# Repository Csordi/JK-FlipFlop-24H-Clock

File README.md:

# JK-FlipFlop-24H-Clock
24H TTL Clock only with TTL integrated circuits.

- 24H clock (no AM/PM mode)
- Time format: HH:MM:SS
- Red 7segment displays
- 6-18V DC IN
- Almost fully through-hole design (only one component is SMD)

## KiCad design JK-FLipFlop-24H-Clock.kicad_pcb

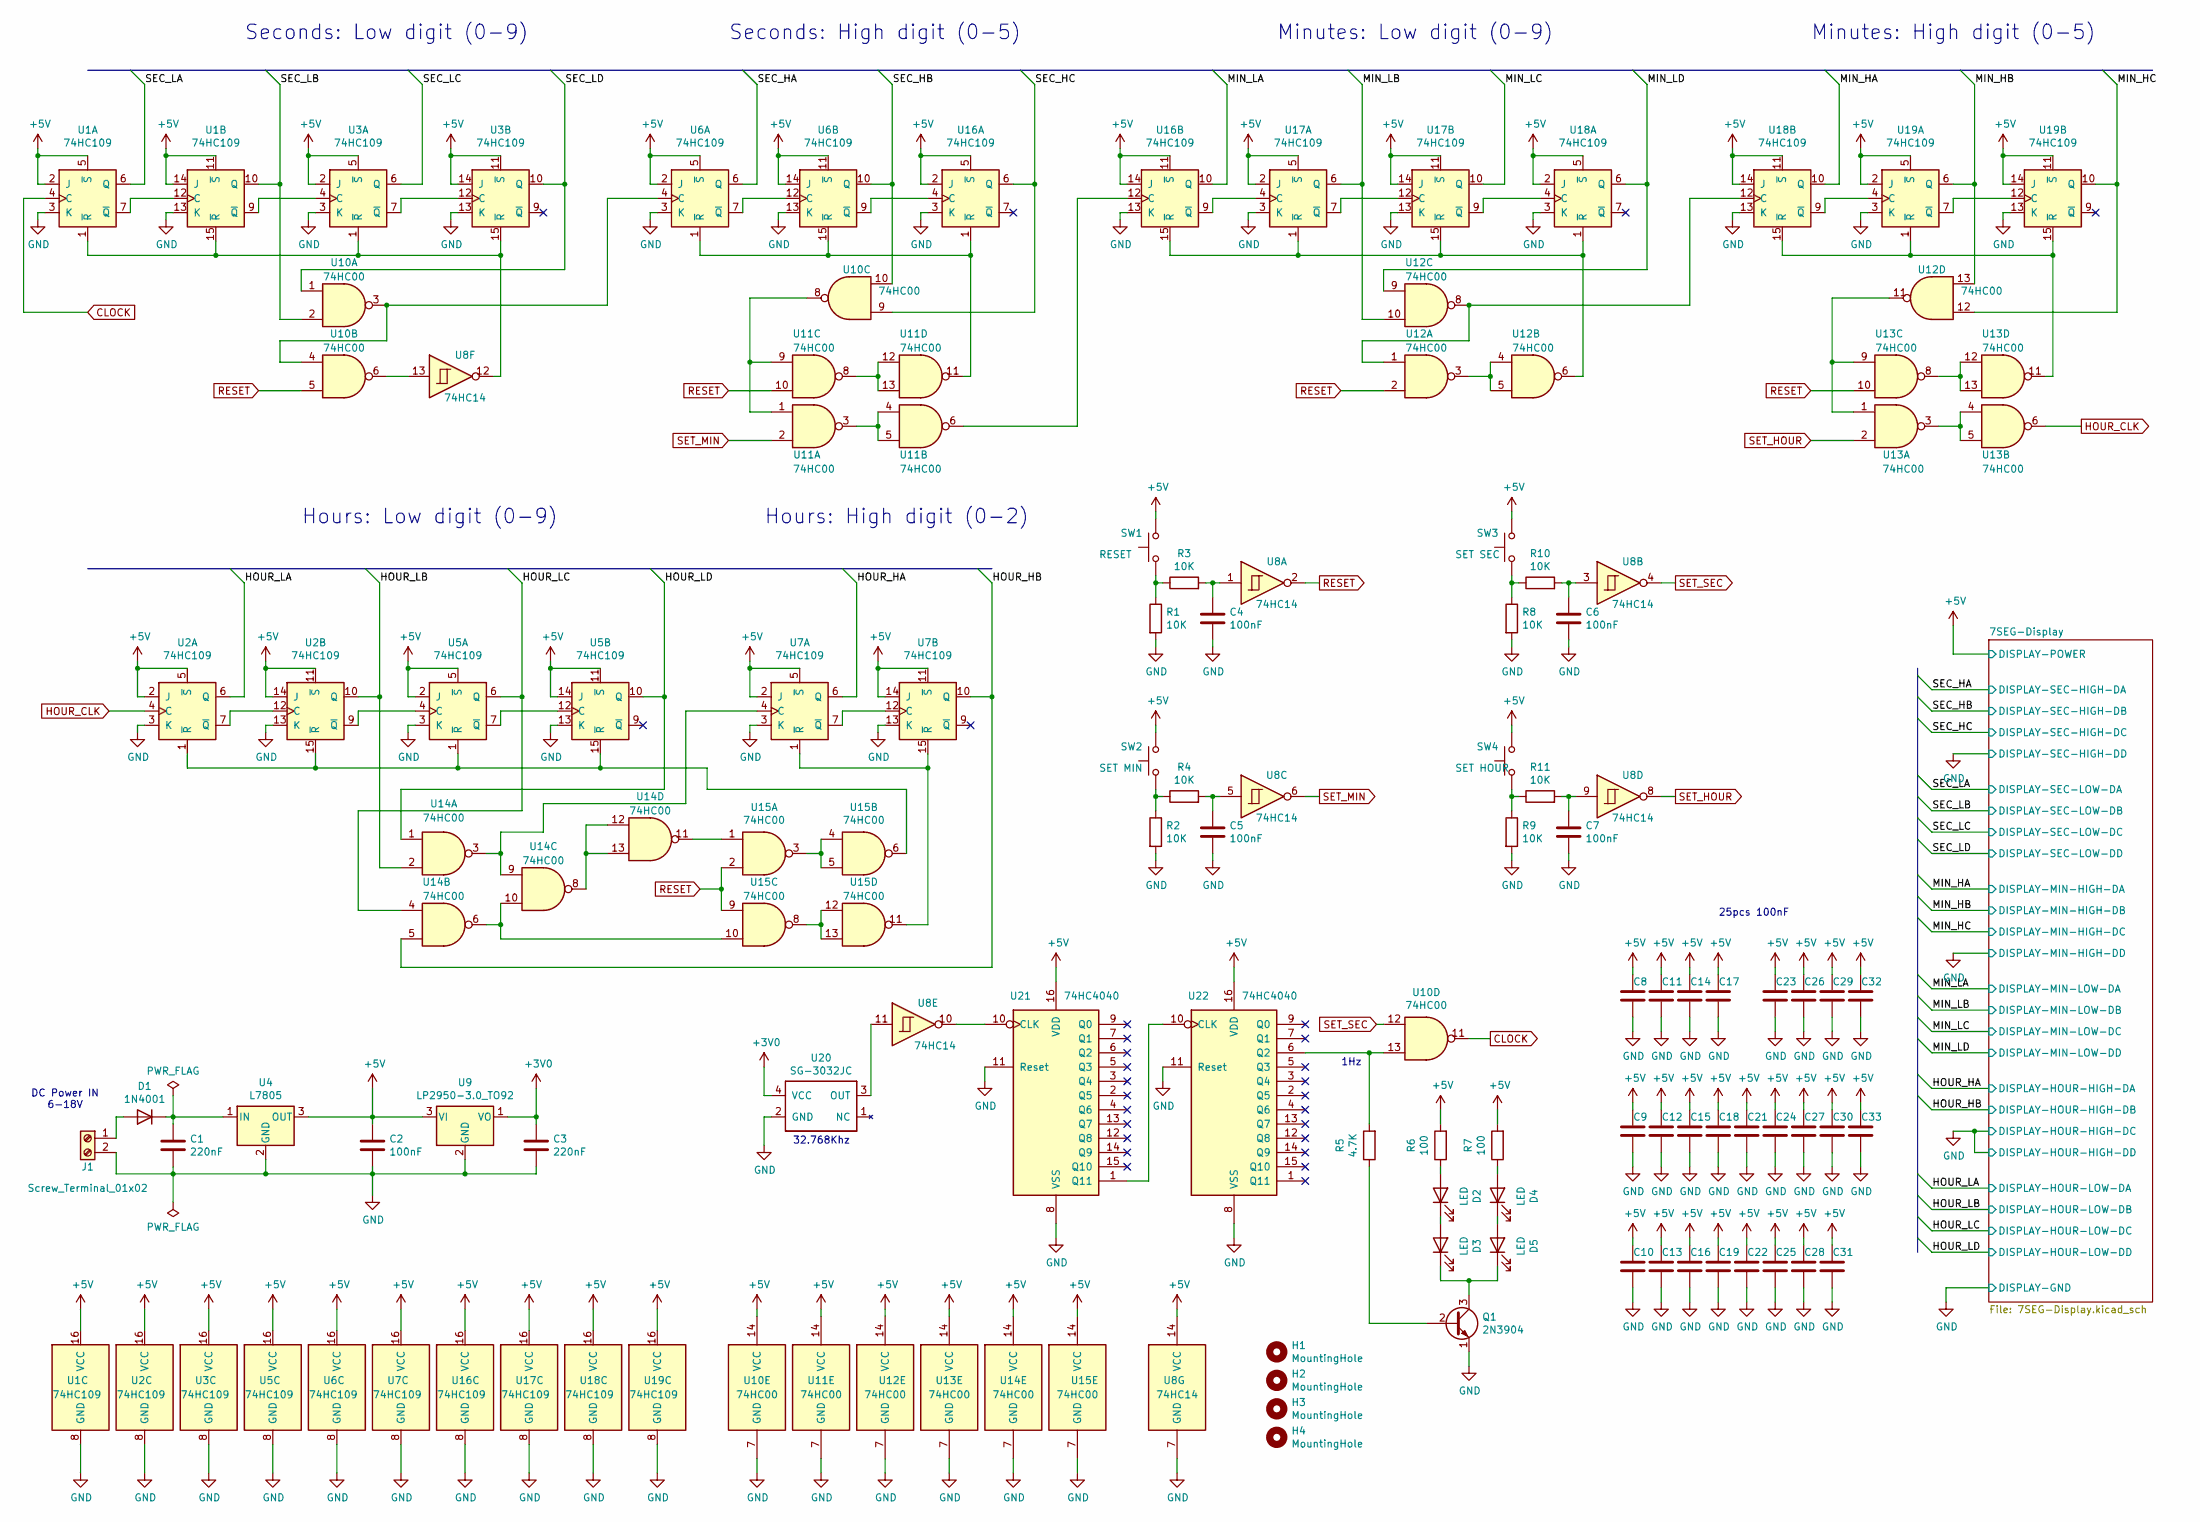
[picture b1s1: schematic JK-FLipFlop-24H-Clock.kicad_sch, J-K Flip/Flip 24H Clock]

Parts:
C1, C3: 220nF; C_Disc_D5.1mm_W3.2mm_P5.00mm
C2, C4, C5, C6, C7, C8, C9, C10, C11, C12, C13, C14, C15, C16, C17, C18, C19, C21, C22, C23, C24, C25, C26, C27, C28, C29, C30, C31, C32, C33: 100nF; C_Disc_D5.1mm_W3.2mm_P5.00mm
D1: 1N4001; D_DO-41_SOD81_P10.16mm_Horizontal
D2, D3, D4, D5: LED; LED_D3.0mm
H1, H2, H3, H4: MountingHole; MountingHole_2.2mm_M2
J1: Screw_Terminal_01x02; TerminalBlock_Altech_AK300-2_P5.00mm
Q1: 2N3904; TO-92_Inline_Wide
R1, R2, R3, R4, R8, R9, R10, R11: 10K; R_Axial_DIN0204_L3.6mm_D1.6mm_P5.08mm_Horizontal
R5: 4.7K; R_Axial_DIN0204_L3.6mm_D1.6mm_P5.08mm_Horizontal
R6, R7: 100; R_Axial_DIN0204_L3.6mm_D1.6mm_P5.08mm_Horizontal
SW1: RESET; SW_PUSH_6mm
SW2: SET MIN; SW_PUSH_6mm
SW3: SET SEC; SW_PUSH_6mm
SW4: SET HOUR; SW_PUSH_6mm
U1, U2, U3, U5, U6, U7, U16, U17, U18, U19: 74HC109; DIP-16_W7.62mm
U4: L7805; TO-220-3_Vertical
U8: 74HC14; DIP-14_W7.62mm
U9: LP2950-3.0_TO92; TO-92_Inline_Wide
U10, U11, U12, U13, U14, U15: 74HC00; DIP-14_W7.62mm
U20: SG-3032JC; SG-3030JC
U21, U22: 74HC4040; DIP-16_W7.62mm

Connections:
+3V0: C3.1, U9.1 (VO), U20.4 (VCC)
+5V: C2.1, C8.1, C9.1, C10.1, C11.1, C12.1, C13.1, C14.1, C15.1, C16.1, C17.1, C18.1, C19.1, C21.1, C22.1, C23.1, C24.1, C25.1, C26.1, C27.1, C28.1, C29.1, C30.1, C31.1, C32.1, C33.1, R6.2, R7.2, SW1.2, SW2.2, SW3.2, SW4.2, U1.2 (J), U1.5 (~S), U1.11 (~S), U1.14 (J), U1.16 (VCC), U2.2 (J), U2.5 (~S), U2.11 (~S), U2.14 (J), U2.16 (VCC), U3.2 (J), U3.5 (~S), U3.11 (~S), U3.14 (J), U3.16 (VCC), U4.3 (OUT), U5.2 (J), U5.5 (~S), U5.11 (~S), U5.14 (J), U5.16 (VCC), U6.2 (J), U6.5 (~S), U6.11 (~S), U6.14 (J), U6.16 (VCC), U7.2 (J), U7.5 (~S), U7.11 (~S), U7.14 (J), U7.16 (VCC), U8.14 (VCC), U9.3 (VI), U10.14 (VCC), U11.14 (VCC), U12.14 (VCC), U13.14 (VCC), U14.14 (VCC), U15.14 (VCC), U16.2 (J), U16.5 (~S), U16.11 (~S), U16.14 (J), U16.16 (VCC), U17.2 (J), U17.5 (~S), U17.11 (~S), U17.14 (J), U17.16 (VCC), U18.2 (J), U18.5 (~S), U18.11 (~S), U18.14 (J), U18.16 (VCC), U19.2 (J), U19.5 (~S), U19.11 (~S), U19.14 (J), U19.16 (VCC), U21.16 (VDD), U22.16 (VDD); also elsewhere on the board
/HOUR_HA: U7.6 (Q); also elsewhere on the board
/HOUR_HB: U7.10 (Q), U14.5; also elsewhere on the board
/HOUR_LA: U2.6 (Q); also elsewhere on the board
/HOUR_LB: U2.10 (Q), U14.2; also elsewhere on the board
/HOUR_LC: U5.6 (Q), U14.4; also elsewhere on the board
/HOUR_LD: U5.10 (Q), U14.1; also elsewhere on the board
/MIN_HA: U18.10 (Q); also elsewhere on the board
/MIN_HB: U12.13, U19.6 (Q); also elsewhere on the board
/MIN_HC: U12.12, U19.10 (Q); also elsewhere on the board
/MIN_LA: U16.10 (Q); also elsewhere on the board
/MIN_LB: U12.10, U17.6 (Q); also elsewhere on the board
/MIN_LC: U17.10 (Q); also elsewhere on the board
/MIN_LD: U12.9, U18.6 (Q); also elsewhere on the board
/SEC_HA: U6.6 (Q); also elsewhere on the board
/SEC_HB: U6.10 (Q), U10.10; also elsewhere on the board
/SEC_HC: U10.9, U16.6 (Q); also elsewhere on the board
/SEC_LA: U1.6 (Q); also elsewhere on the board
/SEC_LB: U1.10 (Q), U10.2; also elsewhere on the board
/SEC_LC: U3.6 (Q); also elsewhere on the board
/SEC_LD: U3.10 (Q), U10.1; also elsewhere on the board
CLOCK: U1.4 (C), U10.11
GND: C1.2, C2.2, C3.2, C4.2, C5.2, C6.2, C7.2, C8.2, C9.2, C10.2, C11.2, C12.2, C13.2, C14.2, C15.2, C16.2, C17.2, C18.2, C19.2, C21.2, C22.2, C23.2, C24.2, C25.2, C26.2, C27.2, C28.2, C29.2, C30.2, C31.2, C32.2, C33.2, J1.2, Q1.1 (E), R1.2, R2.2, R8.2, R9.2, U1.3 (K), U1.8 (GND), U1.13 (K), U2.3 (K), U2.8 (GND), U2.13 (K), U3.3 (K), U3.8 (GND), U3.13 (K), U4.2 (GND), U5.3 (K), U5.8 (GND), U5.13 (K), U6.3 (K), U6.8 (GND), U6.13 (K), U7.3 (K), U7.8 (GND), U7.13 (K), U8.7 (GND), U9.2 (GND), U10.7 (GND), U11.7 (GND), U12.7 (GND), U13.7 (GND), U14.7 (GND), U15.7 (GND), U16.3 (K), U16.8 (GND), U16.13 (K), U17.3 (K), U17.8 (GND), U17.13 (K), U18.3 (K), U18.8 (GND), U18.13 (K), U19.3 (K), U19.8 (GND), U19.13 (K), U20.2 (GND), U21.8 (VSS), U21.11 (Reset), U22.8 (VSS), U22.11 (Reset); also elsewhere on the board
HOUR_CLK: U2.4 (C), U13.6
unnamed: C1.1, D1.1 (K), U4.1 (IN)
unnamed: C4.1, R3.2, U8.1
unnamed: C5.1, R4.2, U8.5
unnamed: C6.1, R10.2, U8.3
unnamed: C7.1, R11.2, U8.9
unnamed: D1.2 (A), J1.1
unnamed: D2.1 (K), D3.2 (A)
unnamed: D2.2 (A), R6.1
unnamed: D3.1 (K), D5.1 (K), Q1.3 (C)
unnamed: D4.1 (K), D5.2 (A)
unnamed: D4.2 (A), R7.1
unnamed: Q1.2 (B), R5.1
unnamed: R1.1, R3.1, SW1.1
unnamed: R2.1, R4.1, SW2.1
unnamed: R5.2, U10.13, U22.6 (Q2)
unnamed: R8.1, R10.1, SW3.1
unnamed: R9.1, R11.1, SW4.1
unnamed: U1.1 (~R), U1.15 (~R), U3.1 (~R), U3.15 (~R), U8.12
unnamed: U1.9 (~Q), U3.4 (C)
unnamed: U1.7 (~Q), U1.12 (C)
unnamed: U2.9 (~Q), U5.4 (C)
unnamed: U2.7 (~Q), U2.12 (C)
unnamed: U3.7 (~Q), U3.12 (C)
unnamed: U5.7 (~Q), U5.12 (C)
unnamed: U6.7 (~Q), U6.12 (C)
unnamed: U7.7 (~Q), U7.12 (C)
unnamed: U6.4 (C), U10.3, U10.4
unnamed: U8.13, U10.6
unnamed: U10.8, U11.1, U11.9
unnamed: U11.3, U11.4, U11.5
unnamed: U11.6, U16.12 (C)
unnamed: U6.1 (~R), U6.15 (~R), U11.11, U16.1 (~R)
unnamed: U11.8, U11.12, U11.13
unnamed: U12.1, U12.8, U18.12 (C)
unnamed: U12.3, U12.4, U12.5
unnamed: U12.6, U16.15 (~R), U17.1 (~R), U17.15 (~R), U18.1 (~R)
unnamed: U12.11, U13.1, U13.9
unnamed: U13.3, U13.4, U13.5
unnamed: U13.11, U18.15 (~R), U19.1 (~R), U19.15 (~R)
unnamed: U13.8, U13.12, U13.13
unnamed: U7.4 (C), U14.3, U14.9
unnamed: U14.6, U14.10, U15.10
unnamed: U14.11, U15.1
unnamed: U14.8, U14.12, U14.13
unnamed: U15.3, U15.4, U15.5
unnamed: U2.1 (~R), U2.15 (~R), U5.1 (~R), U5.15 (~R), U15.6
unnamed: U7.1 (~R), U7.15 (~R), U15.11
unnamed: U15.8, U15.12, U15.13
unnamed: U6.9 (~Q), U16.4 (C)
unnamed: U16.9 (~Q), U17.4 (C)
unnamed: U17.9 (~Q), U18.4 (C)
unnamed: U17.7 (~Q), U17.12 (C)
unnamed: U18.9 (~Q), U19.4 (C)
unnamed: U19.7 (~Q), U19.12 (C)
unnamed: U8.11, U20.3 (OUT)
unnamed: U21.1 (Q11), U22.10 (CLK)
unnamed: U8.10, U21.10 (CLK)
RESET: U8.2, U10.5, U11.10, U12.2, U13.10, U15.2, U15.9
SET_HOUR: U8.8, U13.2
SET_MIN: U8.6, U11.2
SET_SEC: U8.4, U10.12

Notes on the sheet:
Hours: High digit (0-2)
Minutes: High digit (0-5)
Seconds: High digit (0-5)
1Hz
DC Power IN 6-18V
25pcs 100nF
Hours: Low digit (0-9)
32.768Khz
Seconds: Low digit (0-9)
Minutes: Low digit (0-9)

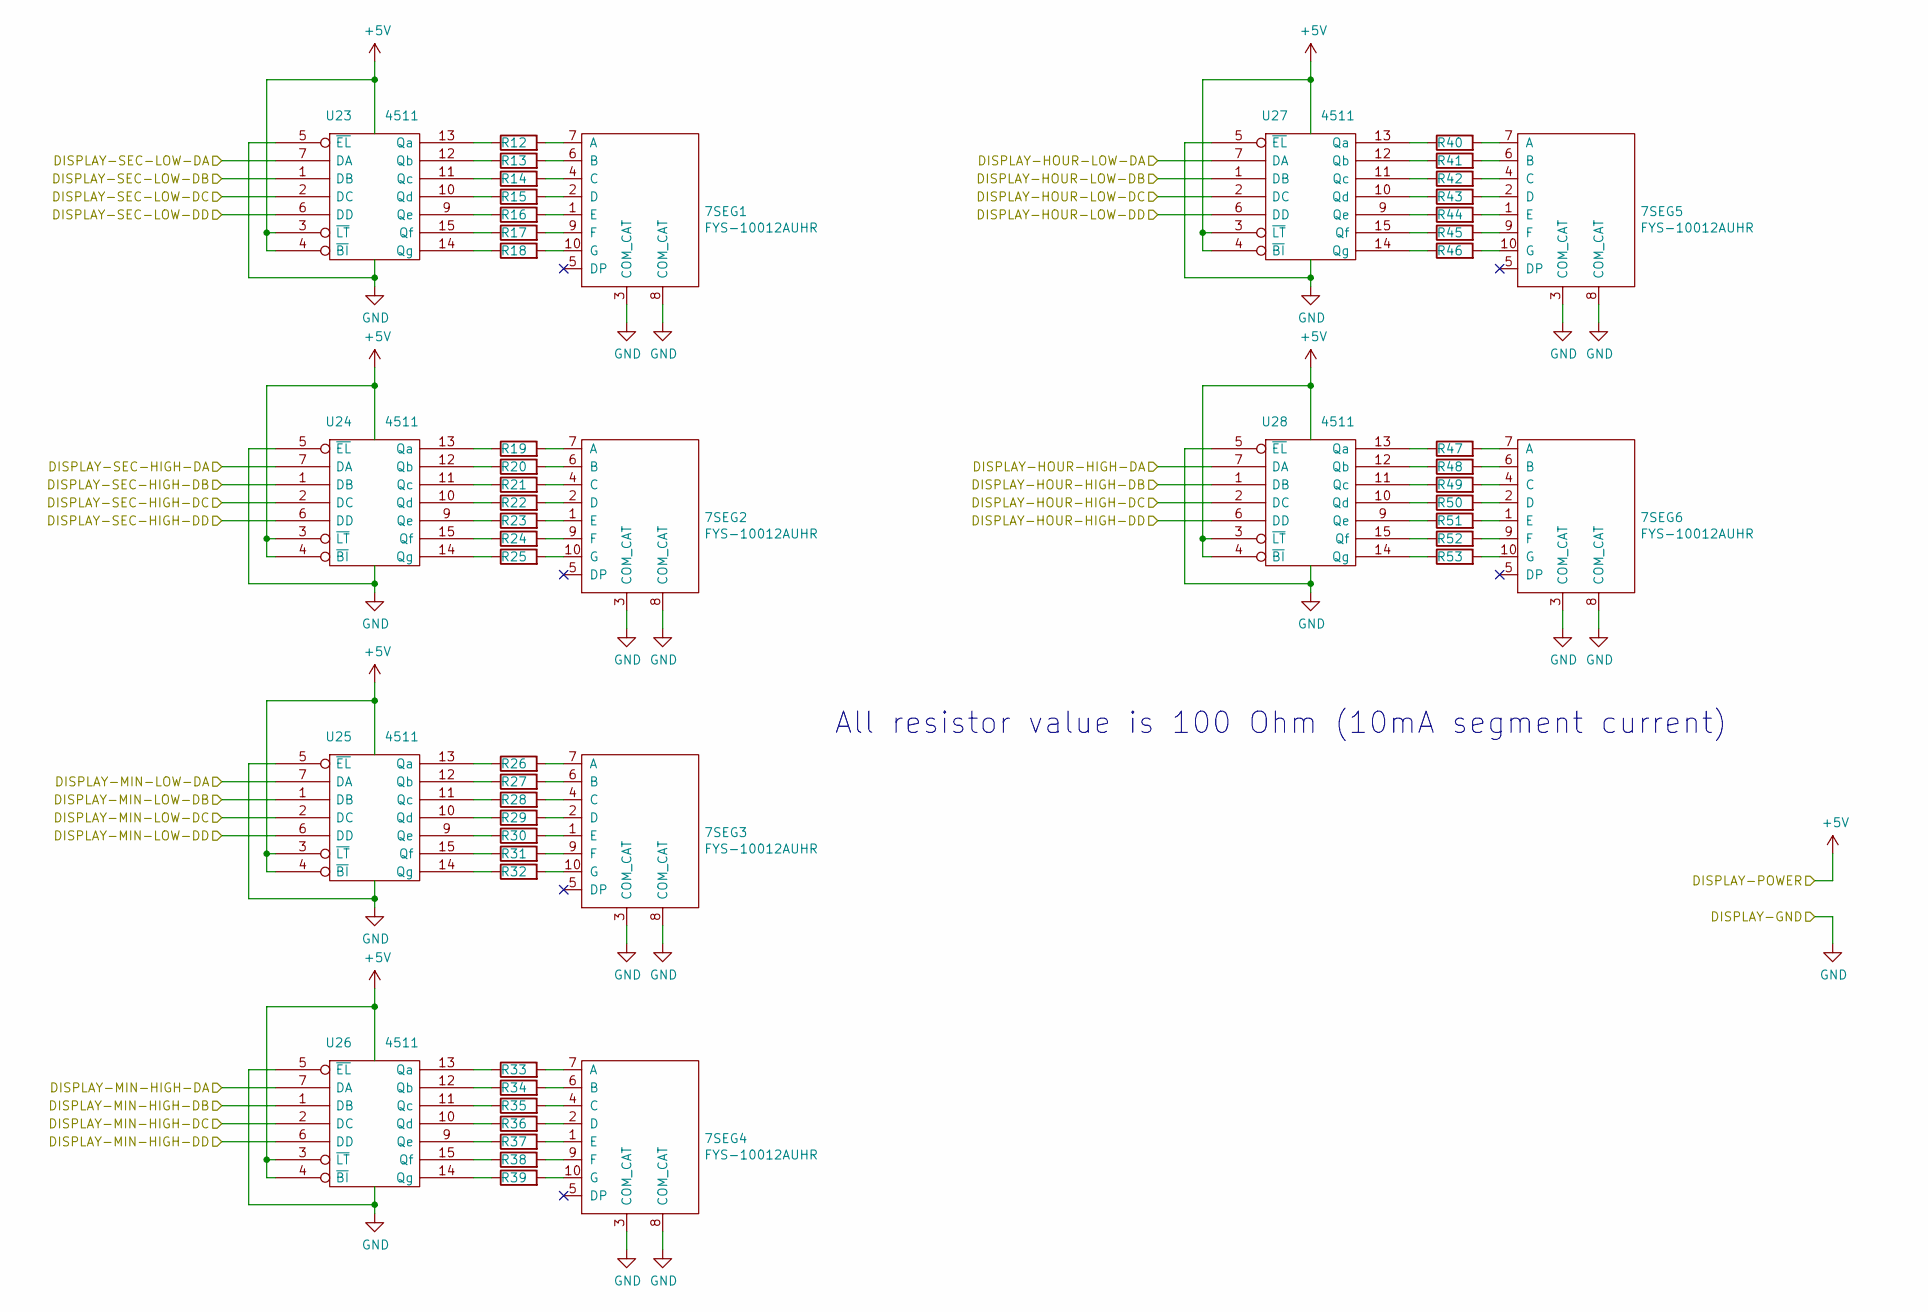
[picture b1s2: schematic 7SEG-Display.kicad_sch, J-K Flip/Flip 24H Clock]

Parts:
7SEG1, 7SEG2, 7SEG3, 7SEG4, 7SEG5, 7SEG6: FYS-10012AUHR; fys-10012auhr
R12, R13, R14, R15, R16, R17, R18, R19, R20, R21, R22, R23, R24, R25, R26, R27, R28, R29, R30, R31, R32, R33, R34, R35, R36, R37, R38, R39, R40, R41, R42, R43, R44, R45, R46, R47, R48, R49, R50, R51, R52, R53: 100; R_Axial_DIN0204_L3.6mm_D1.6mm_P5.08mm_Horizontal
U23, U24, U25, U26, U27, U28: 4511; DIP-16_W7.62mm

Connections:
+5V: U23.3 (~LT), U23.4 (~BI), U23.16 (Vdd), U24.3 (~LT), U24.4 (~BI), U24.16 (Vdd), U25.3 (~LT), U25.4 (~BI), U25.16 (Vdd), U26.3 (~LT), U26.4 (~BI), U26.16 (Vdd), U27.3 (~LT), U27.4 (~BI), U27.16 (Vdd), U28.3 (~LT), U28.4 (~BI), U28.16 (Vdd); also elsewhere on the board
/HOUR_HA: U28.7 (DA); also elsewhere on the board
/HOUR_HB: U28.1 (DB); also elsewhere on the board
/HOUR_LA: U27.7 (DA); also elsewhere on the board
/HOUR_LB: U27.1 (DB); also elsewhere on the board
/HOUR_LC: U27.2 (DC); also elsewhere on the board
/HOUR_LD: U27.6 (DD); also elsewhere on the board
/MIN_HA: U26.7 (DA); also elsewhere on the board
/MIN_HB: U26.1 (DB); also elsewhere on the board
/MIN_HC: U26.2 (DC); also elsewhere on the board
/MIN_LA: U25.7 (DA); also elsewhere on the board
/MIN_LB: U25.1 (DB); also elsewhere on the board
/MIN_LC: U25.2 (DC); also elsewhere on the board
/MIN_LD: U25.6 (DD); also elsewhere on the board
/SEC_HA: U24.7 (DA); also elsewhere on the board
/SEC_HB: U24.1 (DB); also elsewhere on the board
/SEC_HC: U24.2 (DC); also elsewhere on the board
/SEC_LA: U23.7 (DA); also elsewhere on the board
/SEC_LB: U23.1 (DB); also elsewhere on the board
/SEC_LC: U23.2 (DC); also elsewhere on the board
/SEC_LD: U23.6 (DD); also elsewhere on the board
GND: 7SEG1.3 (COM_CAT), 7SEG1.8 (COM_CAT), 7SEG2.3 (COM_CAT), 7SEG2.8 (COM_CAT), 7SEG3.3 (COM_CAT), 7SEG3.8 (COM_CAT), 7SEG4.3 (COM_CAT), 7SEG4.8 (COM_CAT), 7SEG5.3 (COM_CAT), 7SEG5.8 (COM_CAT), 7SEG6.3 (COM_CAT), 7SEG6.8 (COM_CAT), U23.5 (~EL), U23.8 (Vss), U24.5 (~EL), U24.6 (DD), U24.8 (Vss), U25.5 (~EL), U25.8 (Vss), U26.5 (~EL), U26.6 (DD), U26.8 (Vss), U27.5 (~EL), U27.8 (Vss), U28.2 (DC), U28.5 (~EL), U28.6 (DD), U28.8 (Vss); also elsewhere on the board
unnamed: 7SEG1.1 (E), R16.2
unnamed: 7SEG1.2 (D), R15.2
unnamed: 7SEG1.4 (C), R14.2
unnamed: 7SEG1.6 (B), R13.2
unnamed: 7SEG1.7 (A), R12.2
unnamed: 7SEG1.9 (F), R17.2
unnamed: 7SEG1.10 (G), R18.2
unnamed: 7SEG2.1 (E), R23.2
unnamed: 7SEG2.2 (D), R22.2
unnamed: 7SEG2.4 (C), R21.2
unnamed: 7SEG2.6 (B), R20.2
unnamed: 7SEG2.7 (A), R19.2
unnamed: 7SEG2.9 (F), R24.2
unnamed: 7SEG2.10 (G), R25.2
unnamed: 7SEG3.1 (E), R30.2
unnamed: 7SEG3.2 (D), R29.2
unnamed: 7SEG3.4 (C), R28.2
unnamed: 7SEG3.6 (B), R27.2
unnamed: 7SEG3.7 (A), R26.2
unnamed: 7SEG3.9 (F), R31.2
unnamed: 7SEG3.10 (G), R32.2
unnamed: 7SEG4.1 (E), R37.2
unnamed: 7SEG4.2 (D), R36.2
unnamed: 7SEG4.4 (C), R35.2
unnamed: 7SEG4.6 (B), R34.2
unnamed: 7SEG4.7 (A), R33.2
unnamed: 7SEG4.9 (F), R38.2
unnamed: 7SEG4.10 (G), R39.2
unnamed: 7SEG5.1 (E), R44.2
unnamed: 7SEG5.2 (D), R43.2
unnamed: 7SEG5.4 (C), R42.2
unnamed: 7SEG5.6 (B), R41.2
unnamed: 7SEG5.7 (A), R40.2
unnamed: 7SEG5.9 (F), R45.2
unnamed: 7SEG5.10 (G), R46.2
unnamed: 7SEG6.1 (E), R51.2
unnamed: 7SEG6.2 (D), R50.2
unnamed: 7SEG6.4 (C), R49.2
unnamed: 7SEG6.6 (B), R48.2
unnamed: 7SEG6.7 (A), R47.2
unnamed: 7SEG6.9 (F), R52.2
unnamed: 7SEG6.10 (G), R53.2
unnamed: R12.1, U23.13 (Qa)
unnamed: R13.1, U23.12 (Qb)
unnamed: R14.1, U23.11 (Qc)
unnamed: R15.1, U23.10 (Qd)
unnamed: R16.1, U23.9 (Qe)
unnamed: R17.1, U23.15 (Qf)
unnamed: R18.1, U23.14 (Qg)
unnamed: R19.1, U24.13 (Qa)
unnamed: R20.1, U24.12 (Qb)
unnamed: R21.1, U24.11 (Qc)
unnamed: R22.1, U24.10 (Qd)
unnamed: R23.1, U24.9 (Qe)
unnamed: R24.1, U24.15 (Qf)
unnamed: R25.1, U24.14 (Qg)
unnamed: R26.1, U25.13 (Qa)
unnamed: R27.1, U25.12 (Qb)
unnamed: R28.1, U25.11 (Qc)
unnamed: R29.1, U25.10 (Qd)
unnamed: R30.1, U25.9 (Qe)
unnamed: R31.1, U25.15 (Qf)
unnamed: R32.1, U25.14 (Qg)
unnamed: R33.1, U26.13 (Qa)
unnamed: R34.1, U26.12 (Qb)
unnamed: R35.1, U26.11 (Qc)
unnamed: R36.1, U26.10 (Qd)
unnamed: R37.1, U26.9 (Qe)
unnamed: R38.1, U26.15 (Qf)
unnamed: R39.1, U26.14 (Qg)
unnamed: R40.1, U27.13 (Qa)
unnamed: R41.1, U27.12 (Qb)
unnamed: R42.1, U27.11 (Qc)
unnamed: R43.1, U27.10 (Qd)
unnamed: R44.1, U27.9 (Qe)
unnamed: R45.1, U27.15 (Qf)
unnamed: R46.1, U27.14 (Qg)
unnamed: R47.1, U28.13 (Qa)
unnamed: R48.1, U28.12 (Qb)
unnamed: R49.1, U28.11 (Qc)
unnamed: R50.1, U28.10 (Qd)
unnamed: R51.1, U28.9 (Qe)
unnamed: R52.1, U28.15 (Qf)
unnamed: R53.1, U28.14 (Qg)

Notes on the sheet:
All resistor value is 100 Ohm (10mA segment current)

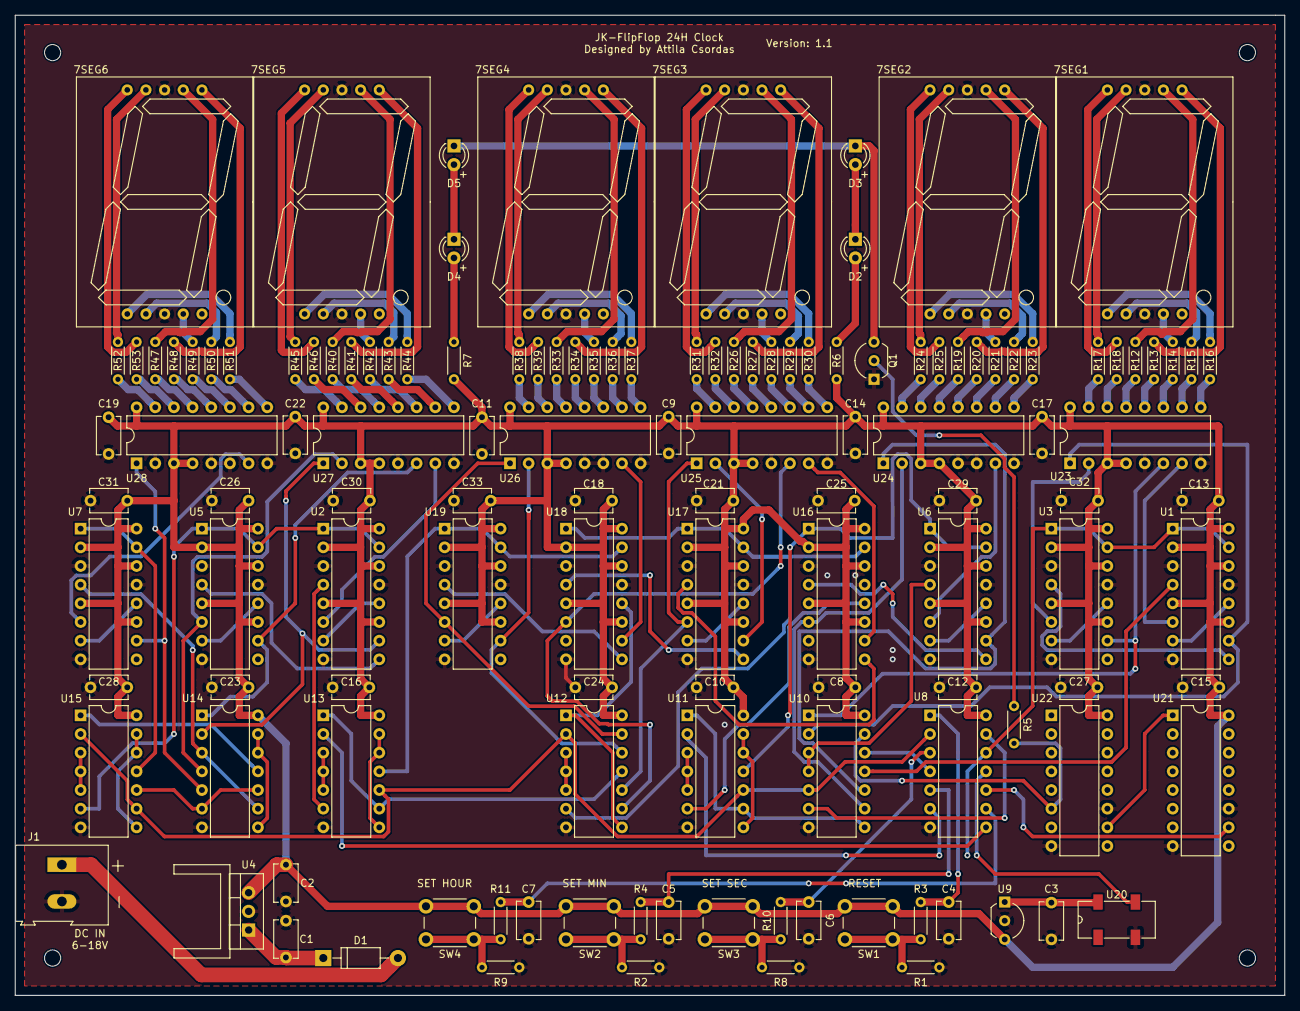
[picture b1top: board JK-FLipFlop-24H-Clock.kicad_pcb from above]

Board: 2 copper layers, 172.7 x 133.3 mm, 134 parts (0 on the bottom side), 170 nets.

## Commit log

2020-05-09 Add files via upload
    Error fix: HOUR digits reset and clock pulse circuit fix
    Optimization: I remove one of the 74HC00
2024-02-14 Simple I2C test C code with MPL3115a2 sensor
    Simple I2C Test with MPL3115a2 sensor.
    C compiler: https://github.com/pcawte/AgDev
2024-03-14 Create LICENSE
2024-03-14 Schematic + PCB Update
